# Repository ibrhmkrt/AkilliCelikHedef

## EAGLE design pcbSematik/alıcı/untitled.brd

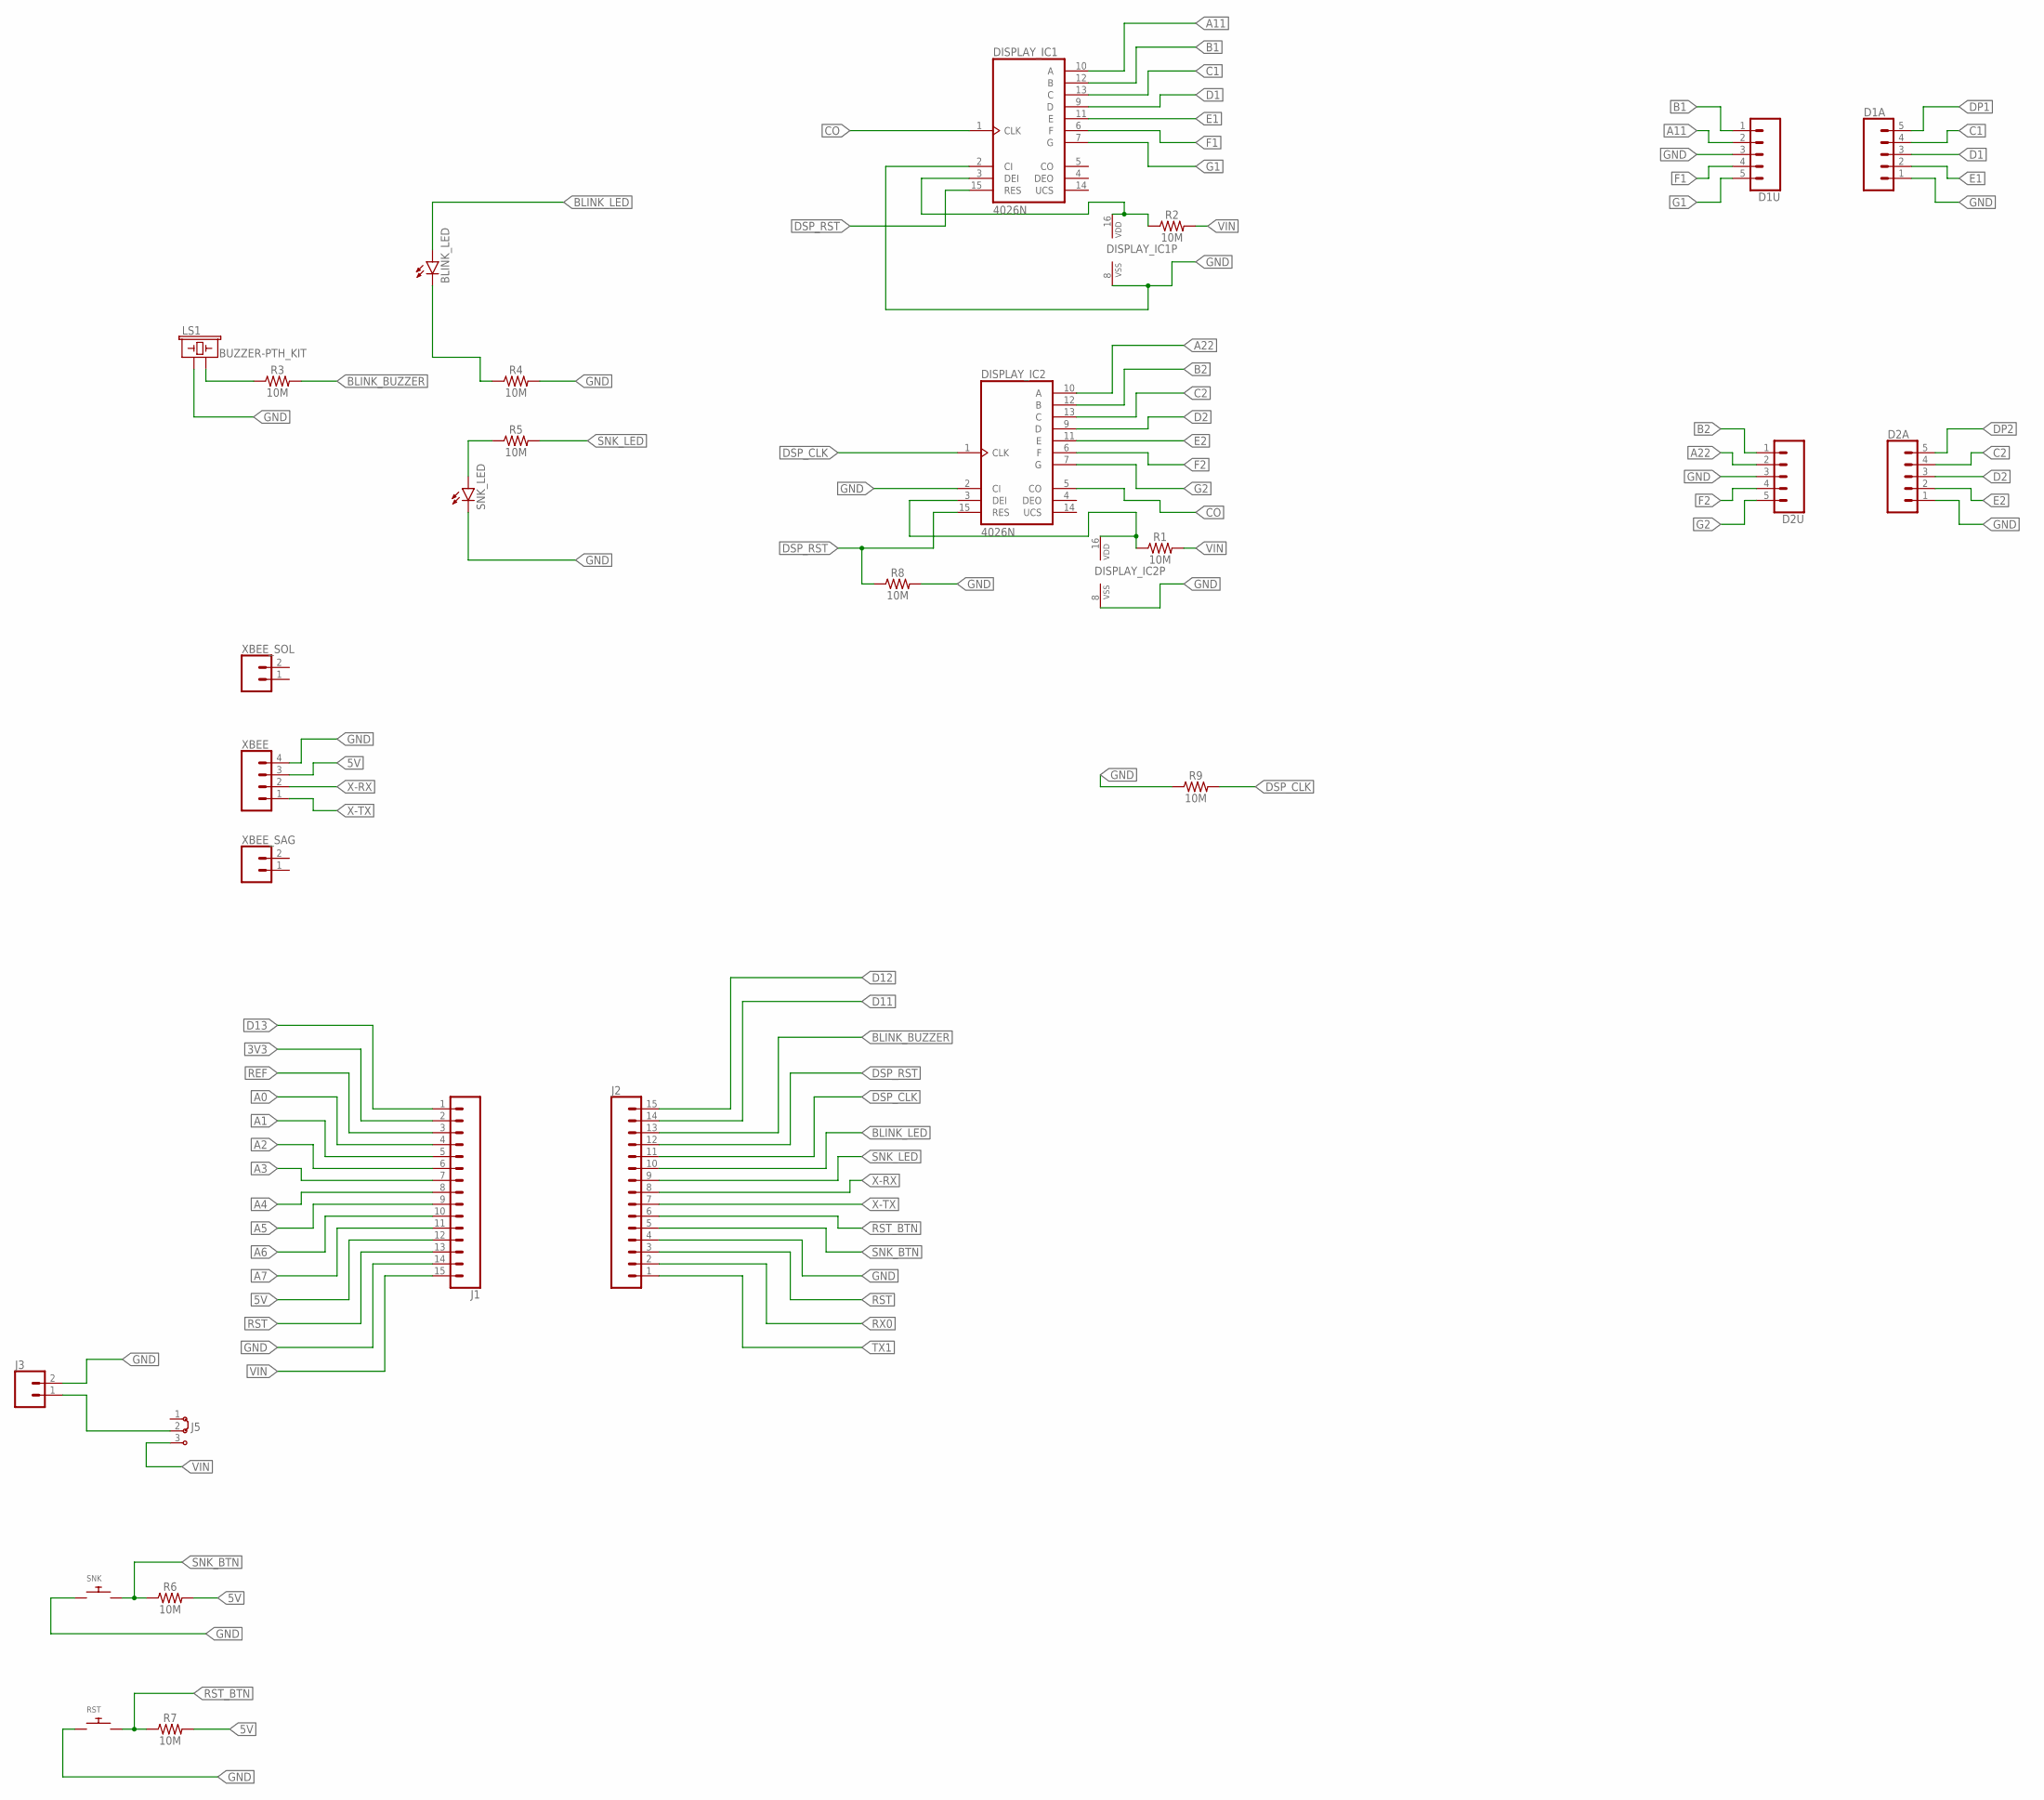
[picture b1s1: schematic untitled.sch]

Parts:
BLINK_LED: LED5MM
D1A, D1U, D2A, D2U: CONN_05; 1X05
DISPLAY_IC1, DISPLAY_IC2: 4026N; DIL16
J1, J2: CONN_15; 1X15
J3: CONN_025MM; SCREWTERMINAL-5MM-2
J5: J2X2MM; 04C
LS1: BUZZER-PTH_KIT; BUZZER-12MM-KIT
R1, R2, R3, R4, R5, R6, R7, R8, R9: 10M; AXIAL-0.3
RST: SWITCH_PUSHBUTTONEVQ-PE; TACT_PANA-EVQ
SNK: SWITCH_PUSHBUTTONEVQ-PE; TACT_PANA-EVQ
SNK_LED: LED5MM
XBEE: CONN_04; 1X04
XBEE_SAG: CONN_02; 1X02
XBEE_SOL: CONN_02; 1X02

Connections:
3V3: J1.2
5V: J1.12, R6.P$2 (2), R7.P$2 (2), XBEE.3
A0: J1.4
A1: J1.5
A2: J1.6
A3: J1.7
A4: J1.8
A5: J1.9
A6: J1.10
A7: J1.11
A11: D1U.2, DISPLAY_IC1.10 (A)
A22: D2U.2, DISPLAY_IC2.10 (A)
B1: D1U.1, DISPLAY_IC1.12 (B)
B2: D2U.1, DISPLAY_IC2.12 (B)
BLINK_BUZZER: J2.13, R3.P$2 (2)
BLINK_LED: BLINK_LED.A, J2.10
BUZZER+: LS1.- (2), R3.P$1 (1)
C1: D1A.4, DISPLAY_IC1.13 (C)
C2: D2A.4, DISPLAY_IC2.13 (C)
CO: DISPLAY_IC1.1 (CLK), DISPLAY_IC2.5 (CO)
D1: D1A.3, DISPLAY_IC1.9 (D)
D2: D2A.3, DISPLAY_IC2.9 (D)
D11: J2.14
D12: J2.15
D13: J1.1
DP1: D1A.5
DP2: D2A.5
DSP_CLK: DISPLAY_IC2.1 (CLK), J2.11, R9.P$2 (2)
DSP_RST: DISPLAY_IC1.15 (RES), DISPLAY_IC2.15 (RES), J2.12, R8.P$1 (1)
E1: D1A.2, DISPLAY_IC1.11 (E)
E2: D2A.2, DISPLAY_IC2.11 (E)
F1: D1U.4, DISPLAY_IC1.6 (F)
F2: D2U.4, DISPLAY_IC2.6 (F)
G1: D1U.5, DISPLAY_IC1.7 (G)
G2: D2U.5, DISPLAY_IC2.7 (G)
GND: D1A.1, D1U.3, D2A.1, D2U.3, DISPLAY_IC1.2 (CI), DISPLAY_IC1.8 (VSS), DISPLAY_IC2.2 (CI), DISPLAY_IC2.8 (VSS), J1.14, J2.4, J3.2, LS1.+ (1), R4.P$2 (2), R8.P$2 (2), R9.P$1 (1), RST.P$1, SNK.P$1, SNK_LED.K (C), XBEE.4
unnamed: R5.P$1 (1), SNK_LED.A
unnamed: BLINK_LED.K (C), R4.P$1 (1)
unnamed: DISPLAY_IC2.3 (DEI), DISPLAY_IC2.16 (VDD), R1.P$1 (1)
unnamed: DISPLAY_IC1.3 (DEI), DISPLAY_IC1.16 (VDD), R2.P$1 (1)
REF: J1.3
RST: J1.13, J2.3
RST_BTN: J2.6, R7.P$1 (1), RST.P$2
RX0: J2.2
SNK_BTN: J2.5, R6.P$1 (1), SNK.P$2
SNK_LED: J2.9, R5.P$2 (2)
TX1: J2.1
VGIRIS: J3.1, J5.2
VIN: J1.15, J5.3, R1.P$2 (2), R2.P$2 (2)
X-RX: J2.8, XBEE.2
X-TX: J2.7, XBEE.1

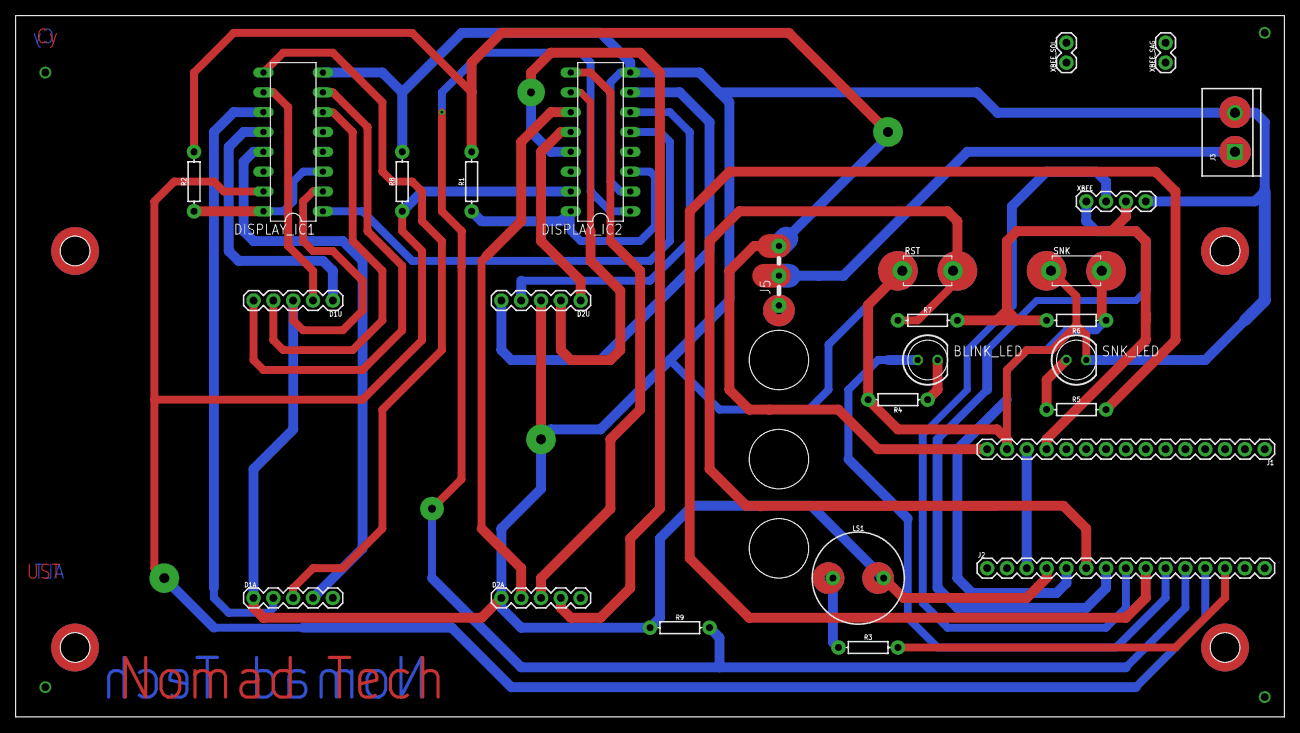
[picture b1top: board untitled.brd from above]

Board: 2 copper layers, 162.5 x 89.8 mm, 27 parts (0 on the bottom side), 34 nets.

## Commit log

2019-10-14 Final

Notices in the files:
parts and their libraries:
SparkFun-Connectors: Licensing: Creative Commons ShareAlike 4.0 International - https://creativecommons.org/licenses/by-sa/4.0
